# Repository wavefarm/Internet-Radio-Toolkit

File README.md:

Wave Farm's Transmission and Sound Art Toolkit

For organizations and Wave Farm Transmit Partners, the Transmission and Sound Art Toolkit is a self-contained kit that enables live audio streaming via WiFi using either the Toolkit’s built-in microphone or line-in audio. The Toolkit communicates with Wave Farm’s Icecast server to provide online audio streaming and automatically records and publishes audio archives. For artists, the Toolkit is an Arduino-based open source expandable platform for telematic performance and remote sonic and physical interaction.

This repo contains the hardware design files in EAGLE CAD format, manufacturing files, Arduino code and enclosure files in OpenSCAD and STL formats.

The project is based on the ESP32W-ROVER platform and the VLSI VS1063 IC.

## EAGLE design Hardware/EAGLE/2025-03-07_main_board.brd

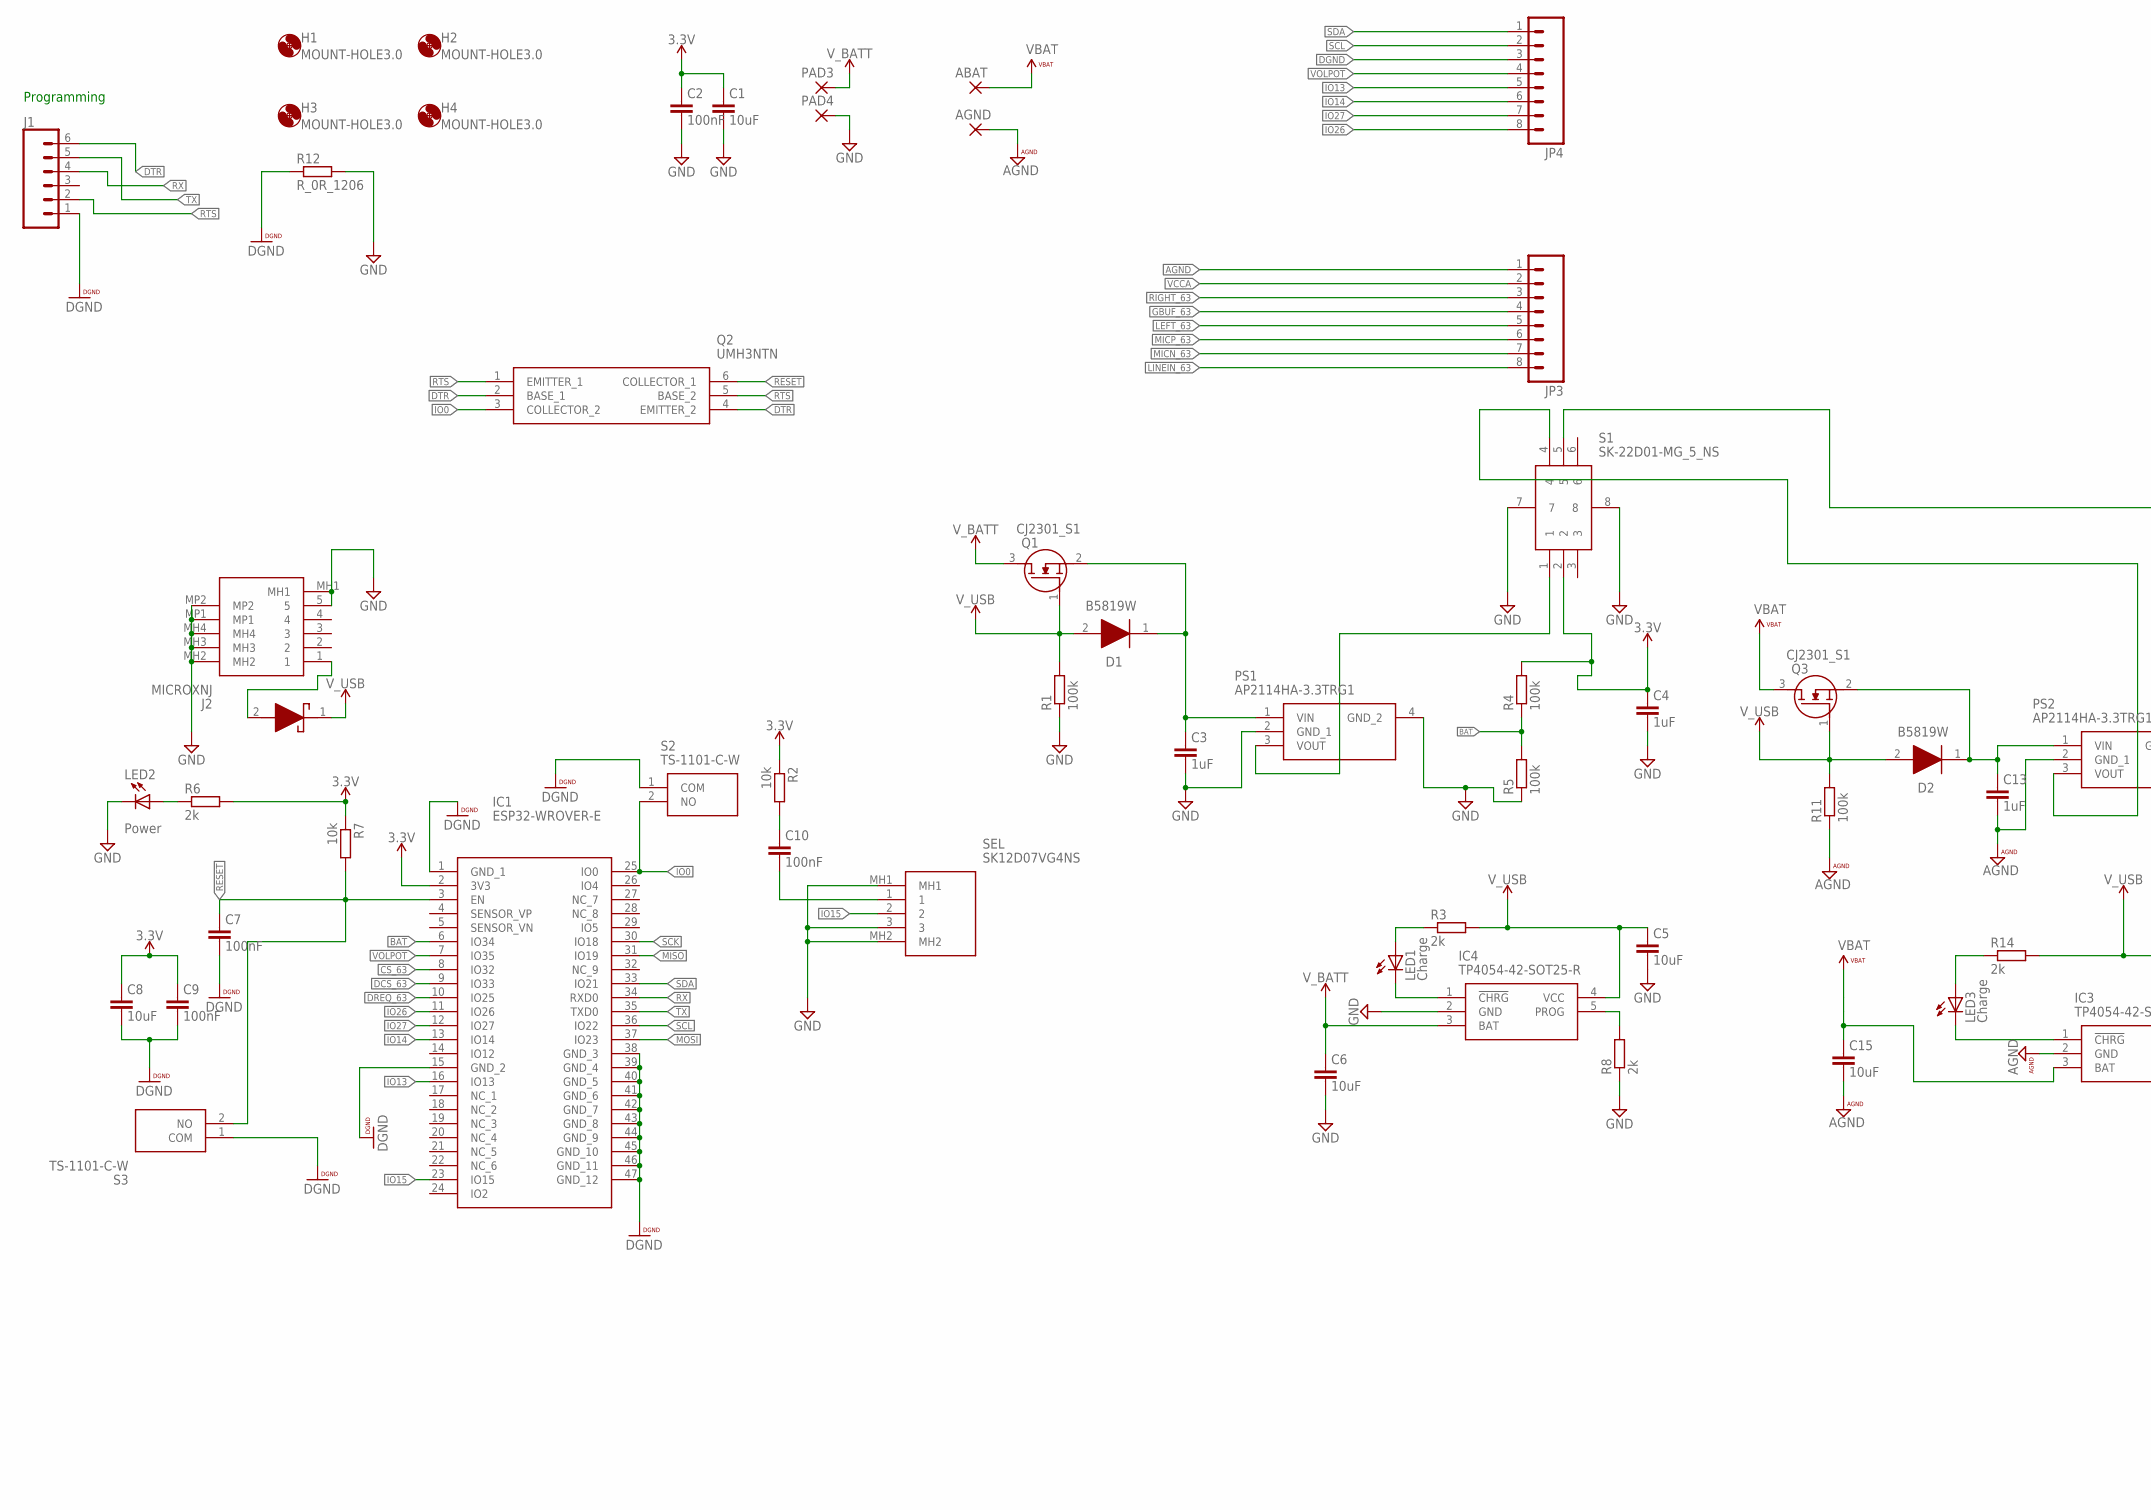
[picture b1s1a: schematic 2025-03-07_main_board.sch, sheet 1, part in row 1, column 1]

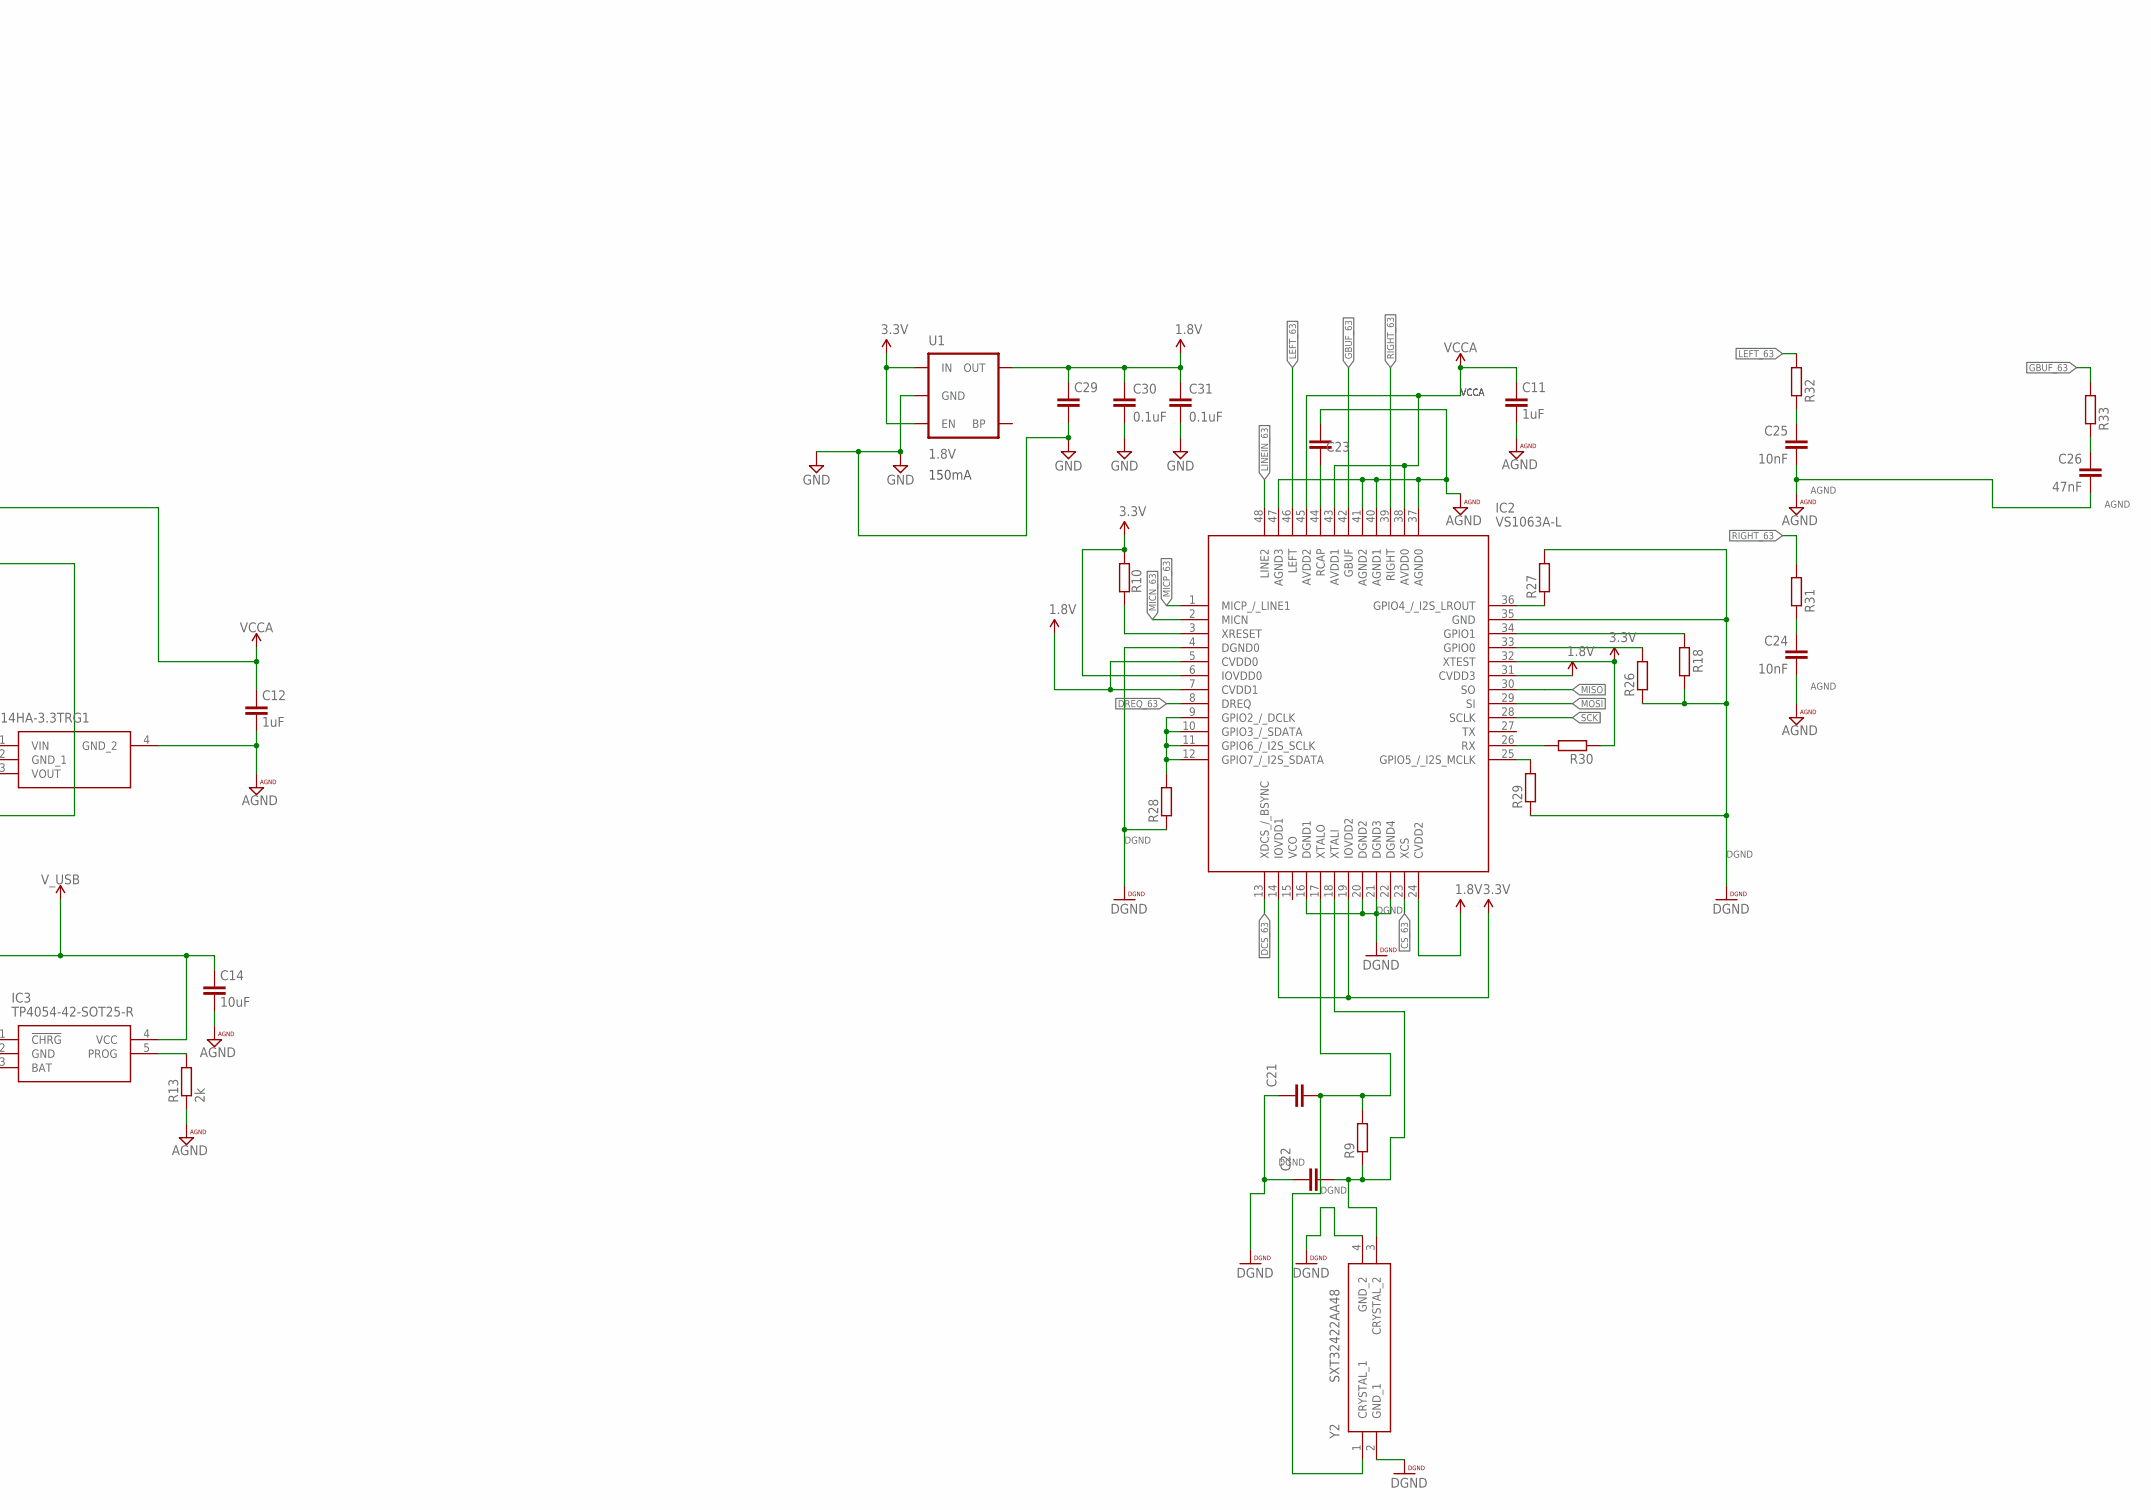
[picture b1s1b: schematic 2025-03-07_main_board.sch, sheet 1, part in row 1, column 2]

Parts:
ABAT: 2,54/0,8
AGND: 2,54/0,8
C1, C5, C6, C8, C14, C15, C29: 10uF; C0603
C2, C7, C9, C10: 100nF; C0603
C3, C4, C11, C12, C13: 1uF; C0402
C21, C22: 22pF; C0603
C23: 1.0uF; C0402
C24, C25: 10nF; 0603-CAP
C26: 47nF; 0603-CAP
C30, C31: 0.1uF; 0603-CAP
D1, D2: B5819W; SOD3716X125N
D5: BAT760-7; SOD2513X120N
H1, H2, H3, H4: MOUNT-HOLE3.0; 3,0
IC1: ESP32-WROVER-E; ESP32WROVERE
IC2: VS1063A-L; QFP50P900X900X160-48N
IC3, IC4: TP4054-42-SOT25-R; SOT95P280X100-5N
J1: CONN_06NO_SILK_FEMALE_PTH; 1X06_NO_SILK
J2: MICROXNJ
JP3, JP4: M08; 1X08_ROUND
LED1, LED3: Charge; CHIP-LED0603
LED2: Power; CHIP-LED0603
PAD3, PAD4: 2,54/0,8
PS1, PS2: AP2114HA-3.3TRG1; SOT230P700X180-4N
Q1, Q3: CJ2301_S1; SOT95P240X115-3N
Q2: UMH3NTN
R1, R4, R5, R10, R11, R18, R26, R27, R28, R29, R30: 100k; R0603
R2, R7: 10k; R0603
R3, R6, R8, R13, R14: 2k; R0603
R9: 1M; R0603
R12: R_0R_1206; R1206
R31, R32: 20; R0603
R33: 10; R0603
S1: SK-22D01-MG_5_NS; SK22D01MG5NS
S2, S3: TS-1101-C-W; TS1101CW
SEL: SK12D07VG4NS
U1: 1.8V; SC70
Y2: SXT32422AA48

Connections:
1.8V: C29.1, C30.1, C31.1, IC2.5 (CVDD0), IC2.7 (CVDD1), IC2.24 (CVDD2), IC2.31 (CVDD3), U1.5 (OUT)
3.3V: C1.1, C2.1, C4.1, C8.1, C9.1, IC1.2 (3V3), IC2.6 (IOVDD0), IC2.14 (IOVDD1), IC2.19 (IOVDD2), IC2.32 (XTEST), R2.1, R4.2, R6.2, R7.1, R10.2, R30.1, S1.2, U1.1 (IN), U1.3 (EN)
AGND: AGND.1, C11.2, C12.2, C13.2, C14.2, C15.2, C23.2, C24.2, C25.2, C26.2, IC2.37 (AGND0), IC2.40 (AGND1), IC2.41 (AGND2), IC2.47 (AGND3), IC3.2 (GND), JP3.1, PS2.2 (GND_1), PS2.4 (GND_2), R11.1, R13.1
BAT: IC1.6 (IO34), R4.1, R5.2
CS_63: IC1.8 (IO32), IC2.23 (XCS)
DCS_63: IC1.9 (IO33), IC2.13 (XDCS_/_BSYNC)
DGND: C7.2, C8.2, C9.2, C21.1, C22.1, IC1.1 (GND_1), IC1.15 (GND_2), IC1.38 (GND_3), IC1.39 (GND_4), IC1.40 (GND_5), IC1.41 (GND_6), IC1.42 (GND_7), IC1.43 (GND_8), IC1.44 (GND_9), IC1.45 (GND_10), IC1.46 (GND_11), IC1.47 (GND_12), IC2.4 (DGND0), IC2.16 (DGND1), IC2.20 (DGND2), IC2.21 (DGND3), IC2.22 (DGND4), IC2.35 (GND), J1.1, JP4.3, R12.1, R18.1, R26.1, R27.2, R28.1, R29.1, S2.1 (COM), S3.1 (COM), Y2.2 (GND_1), Y2.4 (GND_2)
DREQ_63: IC1.10 (IO25), IC2.8 (DREQ)
DTR: J1.6, Q2.2 (BASE_1), Q2.4 (EMITTER_2)
GBUF_63: IC2.42 (GBUF), JP3.4, R33.2
GND: C1.2, C2.2, C3.2, C4.2, C5.2, C6.2, C29.2, C30.2, C31.2, IC4.2 (GND), J2.5, J2.MH1, J2.MH2, J2.MH3, J2.MH4, J2.MP1, J2.MP2, LED2.C, PAD4.1, PS1.2 (GND_1), PS1.4 (GND_2), R1.1, R5.1, R8.1, R12.2, S1.7, S1.8, SEL.3, SEL.MH1, SEL.MH2, U1.2 (GND)
IO0: IC1.25 (IO0), Q2.3 (COLLECTOR_2), S2.2 (NO)
IO13: IC1.16 (IO13), JP4.5
IO14: IC1.13 (IO14), JP4.6
IO15: IC1.23 (IO15), SEL.2
IO26: IC1.11 (IO26), JP4.8
IO27: IC1.12 (IO27), JP4.7
LEFT_63: IC2.46 (LEFT), JP3.5, R32.2
LINEIN_63: IC2.48 (LINE2), JP3.8
MICN_63: IC2.2 (MICN), JP3.7
MICP_63: IC2.1 (MICP_/_LINE1), JP3.6
MISO: IC1.31 (IO19), IC2.30 (SO)
MOSI: IC1.37 (IO23), IC2.29 (SI)
unnamed: PS1.3 (VOUT), S1.1
unnamed: C3.1, D1.1 (K), PS1.1 (VIN), Q1.2 (S)
unnamed: LED2.A, R6.1
unnamed: IC4.1 (!CHRG), LED1.C
unnamed: LED1.A, R3.1
unnamed: D5.2 (A), J2.1
unnamed: IC4.5 (PROG), R8.2
unnamed: C13.1, D2.1 (K), PS2.1 (VIN), Q3.2 (S)
unnamed: C10.1, R2.2
unnamed: C10.2, SEL.1
unnamed: IC2.3 (XRESET), R10.1
unnamed: IC2.34 (GPIO1), R18.2
unnamed: IC3.1 (!CHRG), LED3.C
unnamed: LED3.A, R14.1
unnamed: PS2.3 (VOUT), S1.4
unnamed: C21.2, IC2.17 (XTALO), R9.2, Y2.1 (CRYSTAL_1)
unnamed: IC2.36 (GPIO4_/_I2S_LROUT), R27.1
unnamed: IC2.33 (GPIO0), R26.2
unnamed: C22.2, IC2.18 (XTALI), R9.1, Y2.3 (CRYSTAL_2)
unnamed: C23.1, IC2.44 (RCAP)
unnamed: IC2.25 (GPIO5_/_I2S_MCLK), R29.2
unnamed: IC3.5 (PROG), R13.2
unnamed: IC2.9 (GPIO2_/_DCLK), IC2.10 (GPIO3_/_SDATA), IC2.11 (GPIO6_/_I2S_SCLK), IC2.12 (GPIO7_/_I2S_SDATA), R28.2
unnamed: IC2.26 (RX), R30.2
unnamed: C26.1, R33.1
unnamed: C25.1, R32.1
unnamed: C24.1, R31.1
RESET: C7.1, IC1.3 (EN), Q2.6 (COLLECTOR_1), R7.2, S3.2 (NO)
RIGHT_63: IC2.39 (RIGHT), JP3.3, R31.2
RTS: J1.2, Q2.1 (EMITTER_1), Q2.5 (BASE_2)
RX: IC1.34 (RXD0), J1.4
SCK: IC1.30 (IO18), IC2.28 (SCLK)
SCL: IC1.36 (IO22), JP4.2
SDA: IC1.33 (IO21), JP4.1
TX: IC1.35 (TXD0), J1.5
VBAT: ABAT.1, C15.1, IC3.3 (BAT), Q3.3 (D)
VCCA: C11.1, C12.1, IC2.38 (AVDD0), IC2.43 (AVDD1), IC2.45 (AVDD2), JP3.2, S1.5
VOLPOT: IC1.7 (IO35), JP4.4
V_BATT: C6.1, IC4.3 (BAT), PAD3.1, Q1.3 (D)
V_USB: C5.1, C14.1, D1.2 (A), D2.2 (A), D5.1 (K), IC3.4 (VCC), IC4.4 (VCC), Q1.1 (G), Q3.1 (G), R1.2, R3.2, R11.2, R14.2

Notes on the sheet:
Programming
150mA

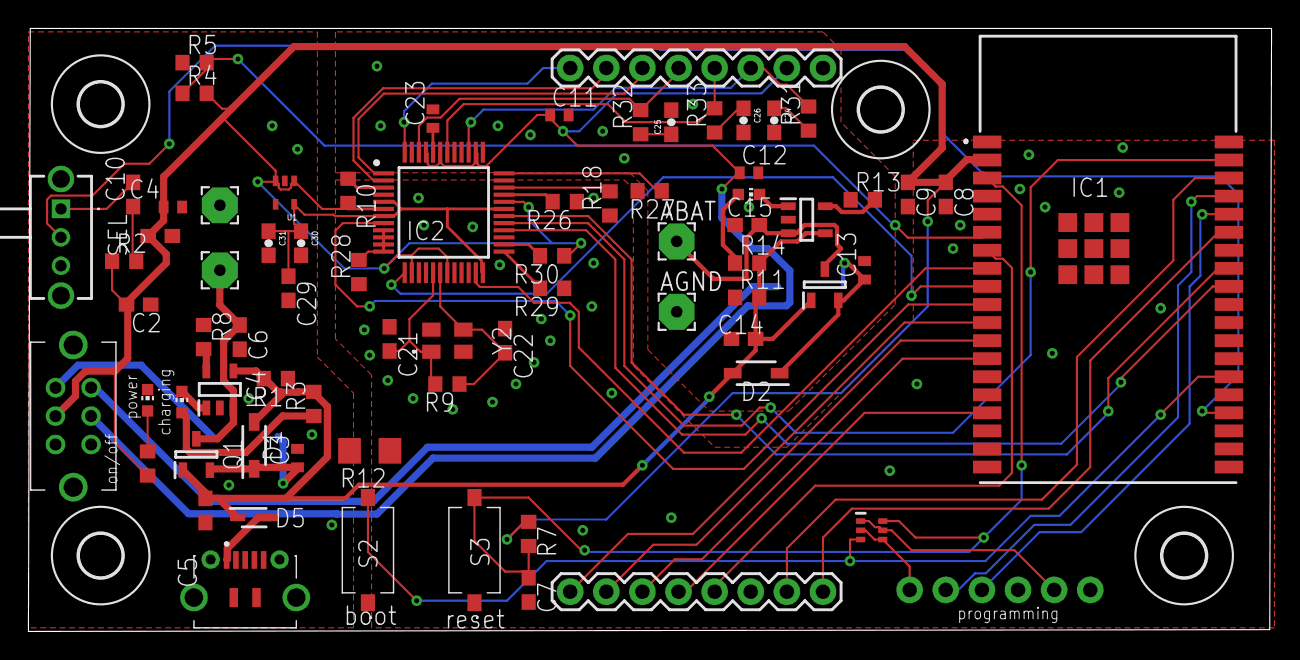
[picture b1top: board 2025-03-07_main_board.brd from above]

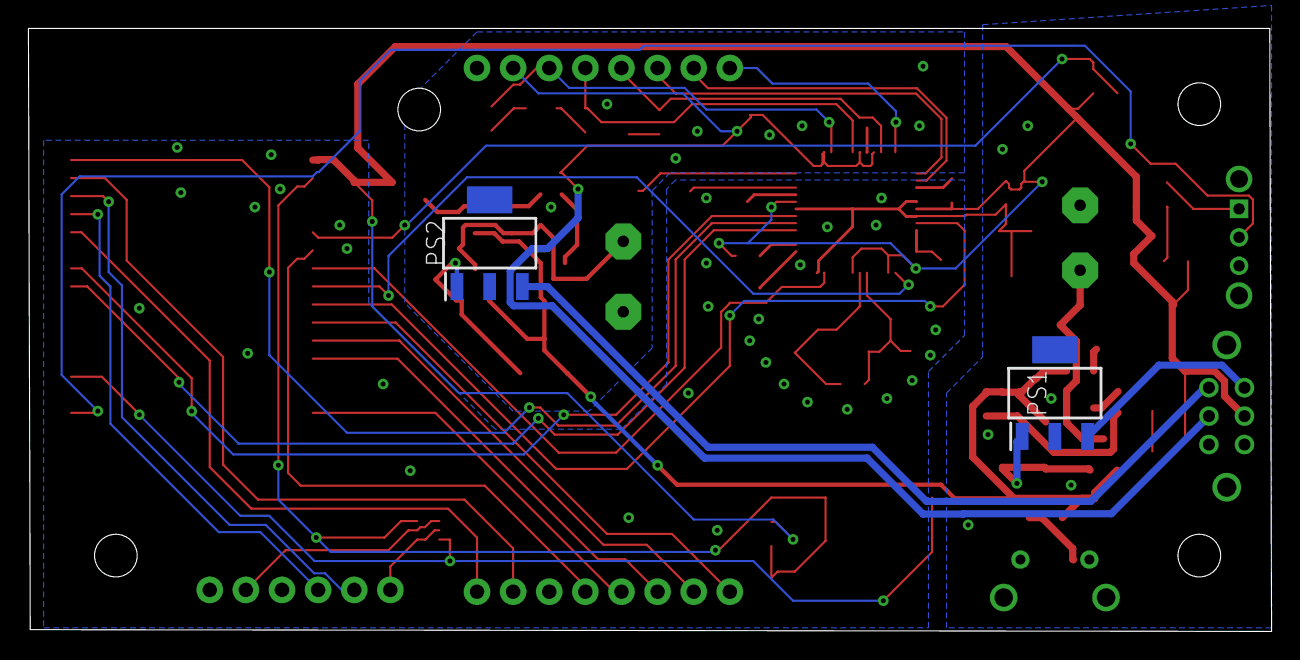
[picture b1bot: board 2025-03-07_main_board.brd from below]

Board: 2 copper layers, 87.4 x 42.4 mm, 80 parts (2 on the bottom side), 63 nets.

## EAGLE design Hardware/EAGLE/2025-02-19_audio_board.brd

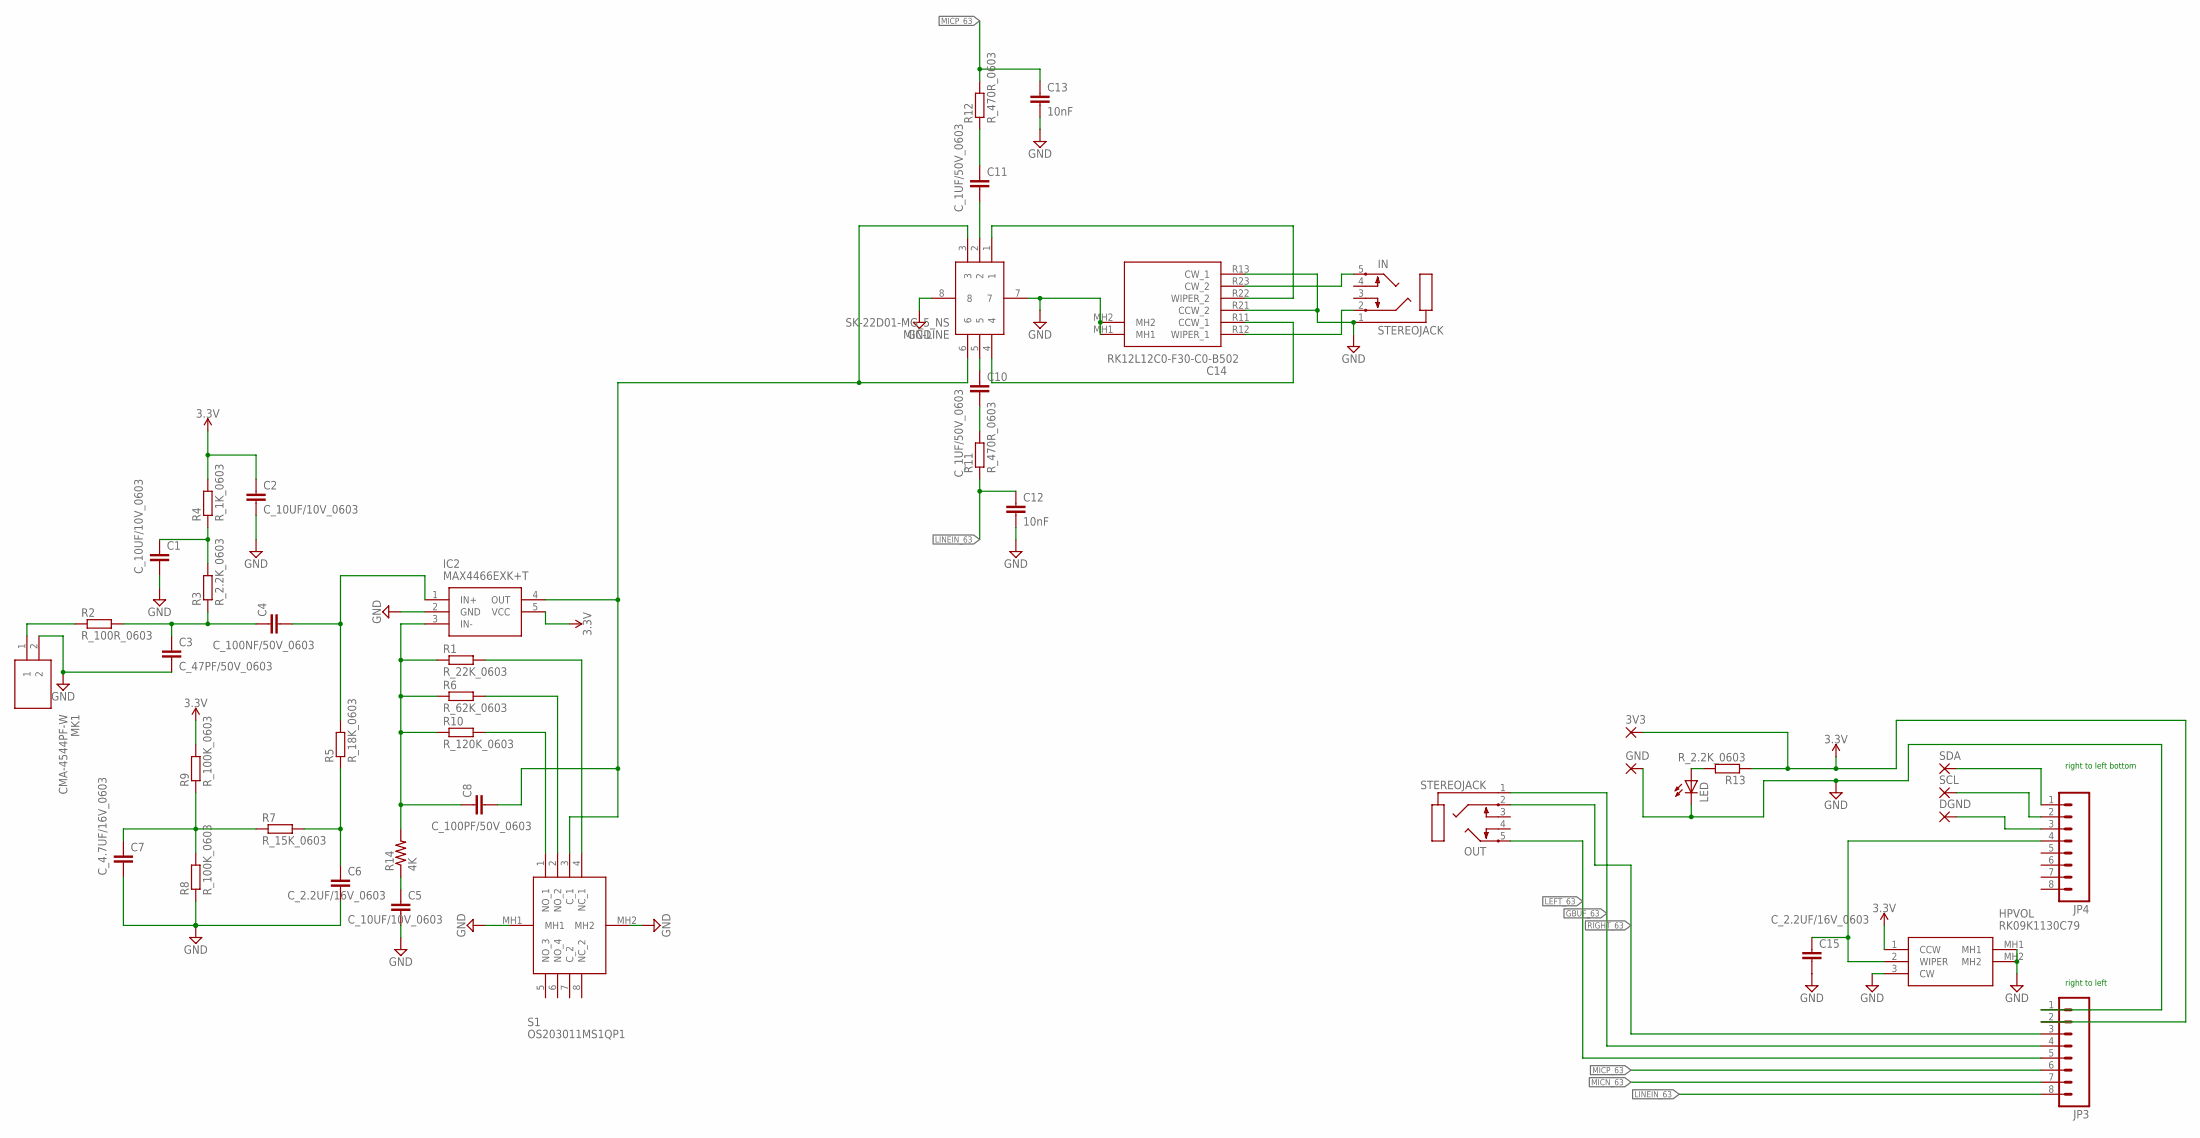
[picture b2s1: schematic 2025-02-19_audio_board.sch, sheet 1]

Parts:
3V3: 2,54/1,0
C1, C2, C5: C_10UF/10V_0603; C0603
C3: C_47PF/50V_0603; C0603
C4: C_100NF/50V_0603; C0603
C6, C15: C_2.2UF/16V_0603; C0603
C7: C_4.7UF/16V_0603; C0603
C8: C_100PF/50V_0603; C0603
C10, C11: C_1UF/50V_0603; C0603
C12, C13: 10nF; 0603
C14: RK12L12C0-F30-C0-B502; RK12L12C0F30C0B502
DGND: 2,54/1,0
GND: 2,54/1,0
HPVOL: RK09K1130C79
IC2: MAX4466EXK+T; SOT65P210X110-5N
IN: STEREOJACK; STX3100
JP3, JP4: M08; 1X08_ROUND
LED: LED; SMARTLED-TTW
MIC-LINE: SK-22D01-MG_5_NS; SK22D01MG5NS
MK1: CMA-4544PF-W; CMA4544PFW
OUT: STEREOJACK; STX3100
R1: R_22K_0603; R0603
R2: R_100R_0603; R0603
R3, R13: R_2.2K_0603; R0603
R4: R_1K_0603; R0603
R5: R_18K_0603; R0603
R6: R_62K_0603; R0603
R7: R_15K_0603; R0603
R8, R9: R_100K_0603; R0603
R10: R_120K_0603; R0603
R11, R12: R_470R_0603; R0603
R14: 4K; R0603
S1: OS203011MS1QP1
SCL: 2,54/1,0
SDA: 2,54/1,0

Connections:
3.3V: 3V3.1, C2.1, HPVOL.1 (CCW), IC2.5 (VCC), JP3.2, R4.2, R9.2, R13.1
GBUF_63: JP3.4, OUT.1
GND: C1.2, C2.2, C3.2, C5.2, C6.2, C7.2, C12.2, C13.2, C14.MH1, C14.MH2, C14.R13 (CW_1), C14.R21 (CCW_2), C15.2, GND.1, HPVOL.3 (CW), HPVOL.MH1, HPVOL.MH2, IC2.2 (GND), IN.1, JP3.1, LED.C@1 (C), MIC-LINE.7, MIC-LINE.8, MK1.2, R8.1, S1.MH1, S1.MH2
LEFT_63: JP3.5, OUT.5
LINEIN_63: C12.1, JP3.8, R11.1
MICN_63: JP3.7
MICP_63: C13.1, JP3.6, R12.2
unnamed: MK1.1, R2.1
unnamed: C3.1, C4.1, R2.2, R3.1
unnamed: LED.A@1 (A), R13.2
unnamed: C5.1, R14.1
unnamed: C6.1, R5.1, R7.2
unnamed: C1.1, R3.2, R4.1
unnamed: C8.1, IC2.3 (IN-), R1.1, R6.1, R10.1, R14.2
unnamed: JP4.1, SDA.1
unnamed: JP4.2, SCL.1
unnamed: R1.2, S1.4 (NC_1)
unnamed: R6.2, S1.2 (NO_2)
unnamed: C11.2, MIC-LINE.2
unnamed: R10.2, S1.1 (NO_1)
unnamed: C10.2, R11.2
unnamed: C10.1, MIC-LINE.5
unnamed: C14.R22 (WIPER_2), MIC-LINE.1
unnamed: C11.1, R12.1
unnamed: C14.R23 (CW_2), IN.5
unnamed: DGND.1, JP4.3
unnamed: C14.R12 (WIPER_1), IN.2
unnamed: C14.R11 (CCW_1), MIC-LINE.4
unnamed: C15.1, HPVOL.2 (WIPER), JP4.4
OAIN: C4.2, IC2.1 (IN+), R5.2
OAOUT: C8.2, IC2.4 (OUT), MIC-LINE.3, MIC-LINE.6, S1.3 (C_1)
RIGHT_63: JP3.3, OUT.2
VHALF: C7.1, R7.1, R8.2, R9.1

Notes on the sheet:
right to left bottom
right to left

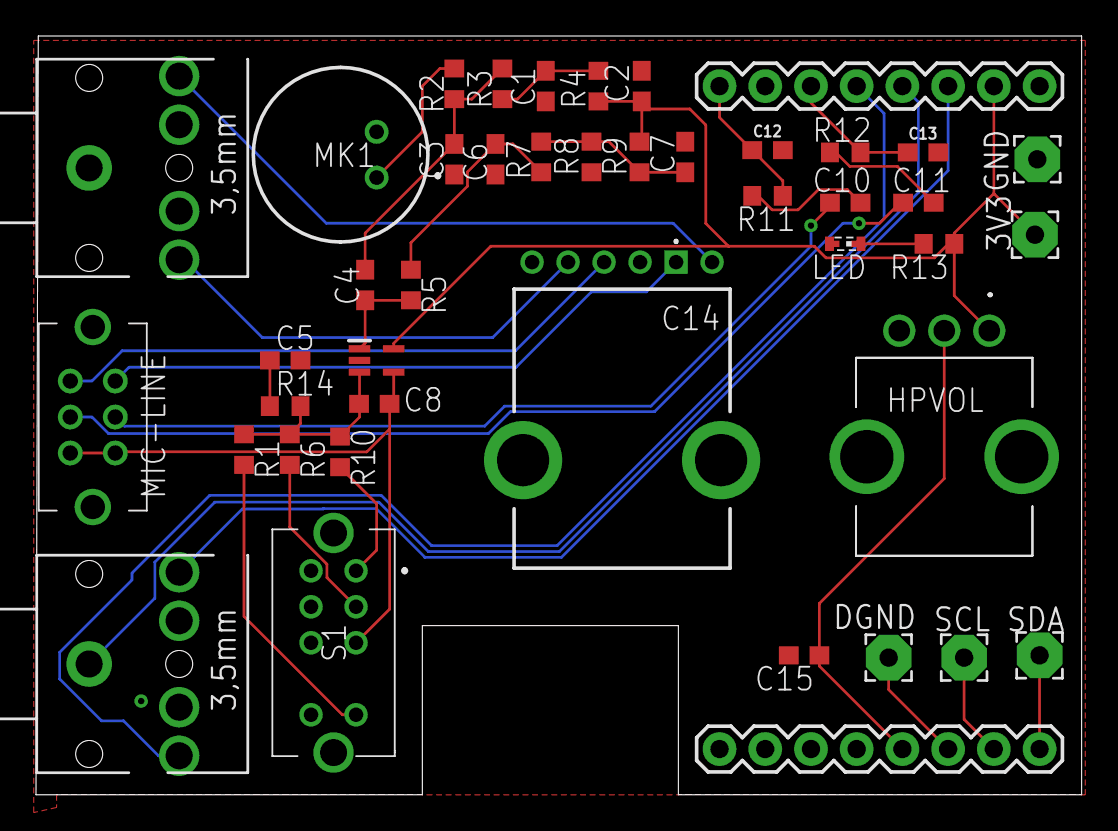
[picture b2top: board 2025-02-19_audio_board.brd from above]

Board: 2 copper layers, 58.1 x 42.2 mm, 43 parts (0 on the bottom side), 32 nets.

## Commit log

2025-10-09 setting up upload premissions
2025-10-09 a okay
2025-10-09 removed mic/line checkbox from index.html .. line is default
2025-10-11 Updated with No Dependecies .. littlefs is now builtin
2025-10-12 tested on Arduino IDE 1.8.19 and 2.3.6 with esp32 1.0.6
2026-04-29 updates to settings to allow for spaces in SSID, html + js updates

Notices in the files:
parts and their libraries:
PatternAgents-ProtoPads: License : http://creativecommons.org/licenses/by-sa/4.0
(Creative Commons 4.0)
SparkFun-Capacitors: Licensing: Creative Commons ShareAlike 4.0 International - https://creativecommons.org/licenses/by-sa/4.0
